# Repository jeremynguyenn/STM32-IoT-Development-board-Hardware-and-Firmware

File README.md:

Relate to this firmware git: https://github.com/jeremynguyenn/My-driver-Embedded-IoT-Frimware.git

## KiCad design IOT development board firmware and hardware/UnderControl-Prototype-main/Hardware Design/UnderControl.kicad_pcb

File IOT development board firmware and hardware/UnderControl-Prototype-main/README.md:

# STM32-GPS-GSM-IoT-Board-UnderControl-
IoT board to control smart home and car systems via Bluetooth, wifi, and GSM with embedded CAN transceiver for OBD.
Note: For Sch, Gerber and assembly files or any info you can contact me.

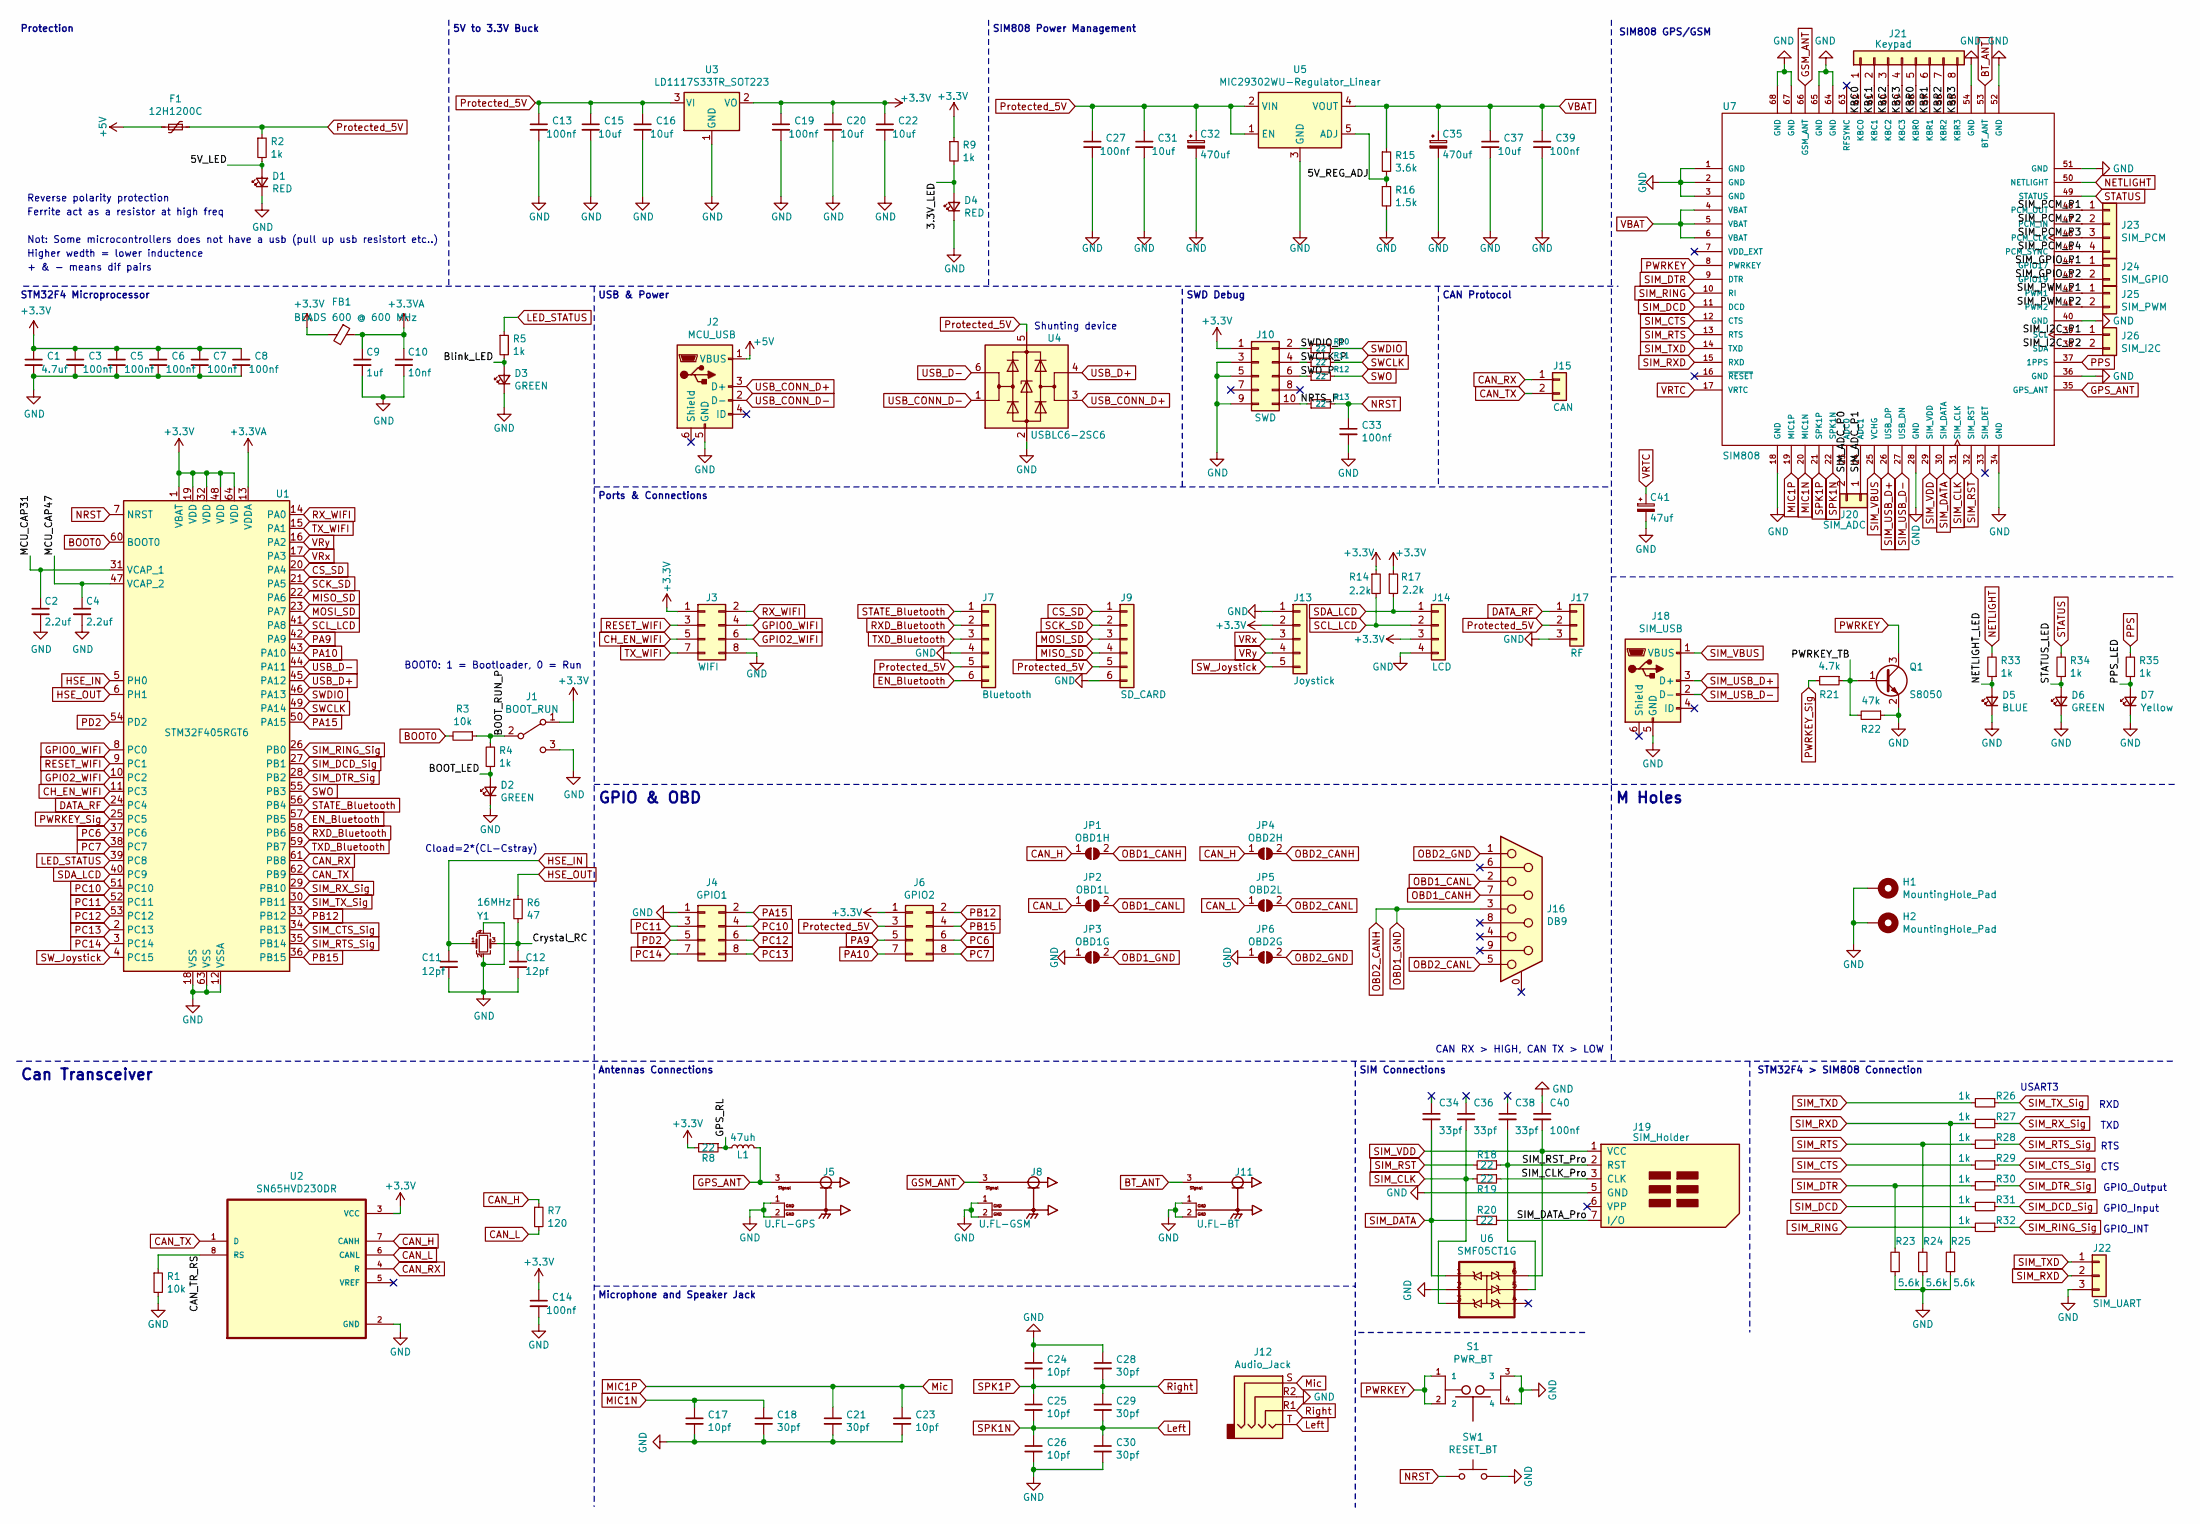
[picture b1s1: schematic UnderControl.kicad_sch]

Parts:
C1: 4.7uf; C_0603_1608Metric; LCSC Part # C19666
C2, C4: 2.2uf; C_0603_1608Metric; LCSC Part # C23630
C3, C5, C6, C7, C8, C13, C14, C19, C27, C33, C39, C40: 100nf; C_0402_1005Metric; LCSC Part # C1525
C9: 1uf; C_0402_1005Metric; LCSC Part # C52923
C10: 10nf; C_0402_1005Metric; LCSC Part # C15195
C11, C12: 12pf; C_0402_1005Metric; LCSC Part # C1547
C15, C16, C20, C22, C31: 10uf; C_0603_1608Metric; LCSC Part # C19702
C17, C23, C24, C25, C26: 10pf; C_0402_1005Metric; LCSC Part # C32949
C18, C21, C28, C29, C30: 30pf; C_0402_1005Metric; LCSC Part # C1570
C32, C35: 470uf; CP_Elec_8x10; LCSC Part # C176671
C34, C36, C38: 33pf; C_0402_1005Metric; LCSC Part # C1562
C37: 10uf; CP_EIA-3216-18_Kemet-A; LCSC Part # C7171
C41: 47uf; C_1206_3216Metric; LCSC Part # C96123
D1, D4: RED; D_0603_1608Metric; LCSC Part # C2286
D2, D6: GREEN; LED_0603_1608Metric; LCSC Part # C72043
D3: GREEN; D_0603_1608Metric; LCSC Part # C72043
D5: BLUE; LED_0603_1608Metric; LCSC Part # C72041
D7: Yellow; LED_0603_1608Metric; LCSC Part # C72038
F1: 12H1200C; Fuse_1206_3216Metric; LCSC Part # C182310
FB1: BEADS 600 @ 600 MHz; L_0805_2012Metric; LCSC Part # C1017
H1, H2: MountingHole_Pad; MountingHole_3.2mm_M3_Pad_Via
J1: BOOT_RUN; PinHeader_1x03_P2.54mm_Vertical
J2: MCU_USB; USB_Micro_JLCPCB; LCSC Part # C404969
J3: WIFI; PinSocket_2x04_P2.54mm_Vertical
J4: GPIO1; PinHeader_2x04_P2.54mm_Vertical
J5: U.FL-GPS; HRS_U.FL-R-SMT(01); LCSC Part # C88374
J6: GPIO2; PinHeader_2x04_P2.54mm_Vertical
J7: Bluetooth; PinSocket_1x06_P2.54mm_Vertical
J8: U.FL-GSM; HRS_U.FL-R-SMT(01); LCSC Part # C88374
J9: SD_CARD; PinSocket_1x06_P2.54mm_Vertical
J10: SWD; PinSocket_2x05_P2.54mm_Vertical
J11: U.FL-BT; HRS_U.FL-R-SMT(01); LCSC Part # C88374
J12: Audio_Jack; Jack_3.5mm_PJ320D_Horizontal
J13: Joystick; PinSocket_1x05_P2.54mm_Vertical
J14: LCD; PinSocket_1x04_P2.54mm_Vertical
J15: CAN; PinSocket_1x02_P2.54mm_Vertical
J16: DB9; DSUB-9_Female_Horizontal_P2.77x2.84mm_EdgePinOffset4.94mm_H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
J17: RF; PinHeader_1x03_P2.54mm_Vertical
J18: SIM_USB; USB_Micro_JLCPCB; LCSC Part # C404969
J19: SIM_Holder; FCI_7111S2015X02LF
J20: SIM_ADC; PinHeader_1x02_P2.54mm_Vertical
J21: Keypad; PinSocket_1x08_P2.54mm_Vertical
J22: SIM_UART; PinHeader_1x03_P2.54mm_Vertical
J23: SIM_PCM; PinHeader_1x04_P2.54mm_Vertical
J24: SIM_GPIO; PinHeader_1x02_P2.54mm_Vertical
J25: SIM_PWM; PinHeader_1x02_P2.54mm_Vertical
J26: SIM_I2C; PinHeader_1x02_P2.54mm_Vertical
JP1: OBD1H; PinHeader_1x02_P2.54mm_Vertical
JP2: OBD1L; PinHeader_1x02_P2.54mm_Vertical
JP3: OBD1G; PinHeader_1x02_P2.54mm_Vertical
JP4: OBD2H; PinHeader_1x02_P2.54mm_Vertical
JP5: OBD2L; PinHeader_1x02_P2.54mm_Vertical
JP6: OBD2G; PinHeader_1x02_P2.54mm_Vertical
L1: 47uh; L_0805_2012Metric; LCSC Part # C14304
Q1: S8050; SOT-23; LCSC Part # C2146
R1, R3: 10k; R_0603_1608Metric; LCSC Part # C25804
R2, R4, R5, R9, R26, R27, R28, R29, R30, R31, R32, R33, R34, R35: 1k; R_0603_1608Metric; LCSC Part # C21190
R6: 47; R_0402_1005Metric; LCSC Part # C25118
R7: 120; R_0603_1608Metric; LCSC Part # C22787
R8, R10, R11, R12, R13, R18, R19, R20: 22; R_0402_1005Metric; LCSC Part # C25092
R14, R17: 2.2k; R_0603_1608Metric; LCSC Part # C4190
R15: 3.6k; R_0603_1608Metric; LCSC Part # C22980
R16: 1.5k; R_0603_1608Metric; LCSC Part # C22843
R21: 4.7k; R_0603_1608Metric; LCSC Part # C23162
R22: 47k; R_0603_1608Metric; LCSC Part # C25819
R23, R24, R25: 5.6k; R_0603_1608Metric; LCSC Part # C23189
S1: PWR_BT; SW_TL3342F160QG
SW1: RESET_BT; SW_1437566-4
U1: STM32F405RGT6; LQFP-64_10x10mm_P0.5mm; LCSC Part # C15742
U2: SN65HVD230DR; SOIC127P599X175-8N; LCSC Part C12084
U3: LD1117S33TR_SOT223; SOT-223-3_TabPin2; LCSC Part C86781
U4: USBLC6-2SC6; SOT-23-6; LCSC Part # C7519
U5: MIC29302WU-Regulator_Linear; TO-263-5_TabPin3; LCSC Part C11149
U6: SMF05CT1G; SOT65P210X110-6N; LCSC Part # C15879
U7: SIM808; XCVR_SIM808
Y1: 16MHz; Crystal_SMD_3225-4Pin_3.2x2.5mm; LCSC Part # C13738

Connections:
+3.3VA: C9.1, C10.1, FB1.1, U1.13 (VDDA)
+3V3: C1.1, C3.1, C5.1, C6.1, C7.1, C8.1, C14.1, C19.1, C20.1, C22.1, FB1.2, J1.1 (A), J3.1, J6.1, J10.1, J13.2, J14.3, R8.2, R9.1, R14.1, R17.1, U1.1 (VBAT), U1.19 (VDD), U1.32 (VDD), U1.48 (VDD), U1.64 (VDD), U2.3 (VCC), U3.2 (VO)
+5V: F1.2, J2.1 (VBUS)
/3.3V_LED: D4.2 (A), R9.2
/5V_LED: D1.2 (A), R2.2
/5V_REG_ADJ: R15.2, R16.1, U5.5 (ADJ)
/BOOT_LED: D2.2 (A), R4.1
/BOOT_RUN_P: J1.2 (B), R3.1, R4.2
/Blink_LED: D3.2 (A), R5.2
/CAN_TR_RS: R1.1, U2.8 (RS)
/Crystal_RC: C12.1, R6.2, Y1.3
/GPS_RL: L1.1, R8.1
/KBC0: J21.1, U7.62 (KBC0)
/KBC1: J21.2, U7.61 (KBC1)
/KBC2: J21.3, U7.60 (KBC2)
/KBC3: J21.4, U7.59 (KBC3)
/KBR0: J21.5, U7.58 (KBR0)
/KBR1: J21.6, U7.57 (KBR1)
/KBR2: J21.7, U7.56 (KBR2)
/KBR3: J21.8, U7.55 (KBR3)
/MCU_CAP31: C2.1, U1.31 (VCAP_1)
/MCU_CAP47: C4.1, U1.47 (VCAP_2)
/NETLIGHT_LED: D5.2 (A), R33.1
/NRTS_P: J10.10, R13.1
/PPS_LED: D7.2 (A), R35.1
/PWRKEY_TB: Q1.1 (B), R21.1, R22.2
/SIM_ADC_P0: J20.2, U7.23 (ADC0)
/SIM_ADC_P1: J20.1, U7.24 (ADC1)
/SIM_CLK_Pro: J19.3 (CLK), R19.1
/SIM_DATA_Pro: J19.7 (I/O), R20.1
/SIM_GPIO_P1: J24.1, U7.44 (GPIO17)
/SIM_GPIO_P2: J24.2, U7.43 (GPIO19)
/SIM_I2C_P1: J26.1, U7.39 (SCL)
/SIM_I2C_P2: J26.2, U7.38 (SDA)
/SIM_PCM_P1: J23.1, U7.48 (PCM_OUT)
/SIM_PCM_P2: J23.2, U7.47 (PCM_IN)
/SIM_PCM_P3: J23.3, U7.46 (PCM_CLK)
/SIM_PCM_P4: J23.4, U7.45 (PCM_SYNC)
/SIM_PWM_P1: J25.1, U7.42 (PWM1)
/SIM_PWM_P2: J25.2, U7.41 (PWM2)
/SIM_RST_Pro: C38.2, J19.2 (RST), R18.1, U6.5
/STATUS_LED: D6.2 (A), R34.1
/SWCLK_P: J10.4, R11.1
/SWDIO_P: J10.2, R10.1
/SWO_P: J10.6, R12.1
BOOT0: R3.2, U1.60 (BOOT0)
BT_ANT: J11.3, U7.53 (BT_ANT)
CAN_H: JP1.1 (A), JP4.1 (A), R7.1, U2.7 (CANH)
CAN_L: JP2.1 (A), JP5.1 (A), R7.2, U2.6 (CANL)
CAN_RX: J15.1, U1.61 (PB8), U2.4 (R)
CAN_TX: J15.2, U1.62 (PB9), U2.1 (D)
CH_EN_WIFI: J3.5, U1.11 (PC3)
CS_SD: J9.1, U1.20 (PA4)
DATA_RF: J17.1, U1.24 (PC4)
EN_Bluetooth: J7.6, U1.57 (PB5)
GND: C1.2, C2.2, C3.2, C4.2, C5.2, C6.2, C7.2, C8.2, C9.2, C10.2, C11.2, C12.2, C13.2, C14.2, C15.2, C16.2, C17.2, C18.2, C19.2, C20.2, C21.2, C22.2, C23.2, C24.1, C26.2, C27.2, C28.1, C30.2, C31.2, C32.2, C33.2, C35.2, C37.2, C39.2, C40.1, C41.2, D1.1 (K), D2.1 (K), D3.1 (K), D4.1 (K), D5.1 (K), D6.1 (K), D7.1 (K), H1.1, H2.1, J1.3 (C), J2.5 (GND), J3.8, J4.1, J5.1, J5.2, J7.4, J8.1, J8.2, J9.6, J10.3, J10.5, J10.9, J11.1, J11.2, J12.R2, J13.1, J14.4, J17.3, J18.5 (GND), J19.5 (GND), J22.3, JP3.1 (A), JP6.1 (A), Q1.2 (E), R1.2, R16.2, R22.1, R23.1, R24.1, R25.1, S1.3, S1.4, SW1.2, U1.12 (VSSA), U1.18 (VSS), U1.63 (VSS), U2.2 (GND), U3.1 (GND), U4.2 (GND), U5.3 (GND), U6.2, U7.1 (GND), U7.2 (GND), U7.3 (GND), U7.18 (GND), U7.28 (GND), U7.34 (GND), U7.36 (GND), U7.40 (GND), U7.51 (GND), U7.52 (GND), U7.54 (GND), U7.64 (GND), U7.65 (GND), U7.67 (GND), U7.68 (GND), Y1.2, Y1.4
GPIO0_WIFI: J3.4, U1.8 (PC0)
GPIO2_WIFI: J3.6, U1.10 (PC2)
GPS_ANT: J5.3, L1.2, U7.35 (GPS_ANT)
GSM_ANT: J8.3, U7.66 (GSM_ANT)
HSE_IN: C11.1, U1.5 (PH0), Y1.1
HSE_OUT: R6.1, U1.6 (PH1)
LED_STATUS: R5.1, U1.39 (PC8)
Left: C25.2, C26.1, C29.2, C30.1, J12.T, U7.22 (SPK1N)
MIC1N: C17.1, C18.1, U7.20 (MIC1N)
MIC1P: C21.1, C23.1, J12.S, U7.19 (MIC1P)
MISO_SD: J9.4, U1.22 (PA6)
MOSI_SD: J9.3, U1.23 (PA7)
NETLIGHT: R33.2, U7.50 (NETLIGHT)
NRST: C33.1, R13.2, SW1.1, U1.7 (NRST)
OBD1_CANH: J16.7, JP1.2 (B)
OBD1_CANL: J16.2, JP2.2 (B)
OBD1_GND: J16.3, JP3.2 (B), JP4.2 (B)
OBD2_CANL: J16.5, JP5.2 (B)
OBD2_GND: J16.1, JP6.2 (B)
PA9: J6.5, U1.42 (PA9)
PA10: J6.7, U1.43 (PA10)
PA15: J4.2, U1.50 (PA15)
PB12: J6.2, U1.33 (PB12)
PB15: J6.4, U1.36 (PB15)
PC6: J6.6, U1.37 (PC6)
PC7: J6.8, U1.38 (PC7)
PC10: J4.4, U1.51 (PC10)
PC11: J4.3, U1.52 (PC11)
PC12: J4.6, U1.53 (PC12)
PC13: J4.8, U1.2 (PC13)
PC14: J4.7, U1.3 (PC14)
PD2: J4.5, U1.54 (PD2)
PPS: R35.2, U7.37 (1PPS)
PWRKEY: Q1.3 (C), S1.1, S1.2, U7.8 (PWRKEY)
PWRKEY_Sig: R21.2, U1.25 (PC5)
Protected_5V: C13.1, C15.1, C16.1, C27.1, C31.1, C32.1, F1.1, J6.3, J7.5, J9.5, J17.2, R2.1, U3.3 (VI), U4.5 (VBUS), U5.1 (EN), U5.2 (VIN)
RESET_WIFI: J3.3, U1.9 (PC1)
RXD_Bluetooth: J7.2, U1.58 (PB6)
RX_WIFI: J3.2, U1.14 (PA0)
Right: C24.2, C25.1, C28.2, C29.1, J12.R1, U7.21 (SPK1P)
SCK_SD: J9.2, U1.21 (PA5)
SCL_LCD: J14.2, R14.2, U1.41 (PA8)
SDA_LCD: J14.1, R17.2, U1.40 (PC9)
SIM_CLK: C36.2, R19.2, U6.3, U7.31 (SIM_CLK)
SIM_CTS: R29.2, U7.12 (CTS)
SIM_CTS_Sig: R29.1, U1.34 (PB13)
SIM_DATA: C34.2, R20.2, U6.1, U7.30 (SIM_DATA)
SIM_DCD: R31.2, U7.11 (DCD)
SIM_DCD_Sig: R31.1, U1.27 (PB1)
SIM_DTR: R23.2, R30.2, U7.9 (DTR)
SIM_DTR_Sig: R30.1, U1.28 (PB2)
SIM_RING: R32.2, U7.10 (RI)
SIM_RING_Sig: R32.1, U1.26 (PB0)
SIM_RST: R18.2, U7.32 (SIM_RST)
SIM_RTS: R24.2, R28.2, U7.13 (RTS)
SIM_RTS_Sig: R28.1, U1.35 (PB14)
SIM_RXD: J22.2, R25.2, R27.2, U7.15 (RXD)
SIM_RX_Sig: R27.1, U1.29 (PB10)
SIM_TXD: J22.1, R26.2, U7.14 (TXD)
SIM_TX_Sig: R26.1, U1.30 (PB11)
SIM_USB_D+: J18.3 (D+), U7.26 (USB_DP)
SIM_USB_D-: J18.2 (D-), U7.27 (USB_DN)
SIM_VBUS: J18.1 (VBUS), U7.25 (VCHG)
SIM_VDD: C40.2, J19.1 (VCC), U6.6, U7.29 (SIM_VDD)
STATE_Bluetooth: J7.1, U1.56 (PB4)
STATUS: R34.2, U7.49 (STATUS)
SWCLK: R11.2, U1.49 (PA14)
SWDIO: R10.2, U1.46 (PA13)
SWO: R12.2, U1.55 (PB3)
SW_Joystick: J13.5, U1.4 (PC15)
TXD_Bluetooth: J7.3, U1.59 (PB7)
TX_WIFI: J3.7, U1.15 (PA1)
USB_CONN_D+: J2.3 (D+), U4.3 (I/O2)
USB_CONN_D-: J2.2 (D-), U4.1 (I/O1)
USB_D+: U1.45 (PA12), U4.4 (I/O2)
USB_D-: U1.44 (PA11), U4.6 (I/O1)
VBAT: C35.1, C37.1, C39.1, R15.1, U5.4 (VOUT), U7.4 (VBAT), U7.5 (VBAT), U7.6 (VBAT)
VRTC: C41.1, U7.17 (VRTC)
VRx: J13.3, U1.17 (PA3)
VRy: J13.4, U1.16 (PA2)

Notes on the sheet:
Protection
STM32F4 Microprocessor
Can Transceiver
Reverse polarity protection
Ferrite act as a resistor at high freq
Not: Some microcontrollers does not have a usb (pull up usb resistort etc..)
Higher wedth = lower inductence
+ & - means dif pairs
BOOT0: 1 = Bootloader, 0 = Run
Cload=2*(CL-Cstray)
5V to 3.3V Buck
USB & Power
Ports & Connections
GPIO & OBD
Antennas Connections
Microphone and Speaker Jack
SIM808 Power Management
Shunting device
SWD Debug
SIM Connections
CAN RX > HIGH, CAN TX > LOW
CAN Protocol
M Holes
SIM808 GPS/GSM
STM32F4 > SIM808 Connection
USART3
GPIO_Output
GPIO_Input
GPIO_INT
RXD
TXD
RTS
CTS

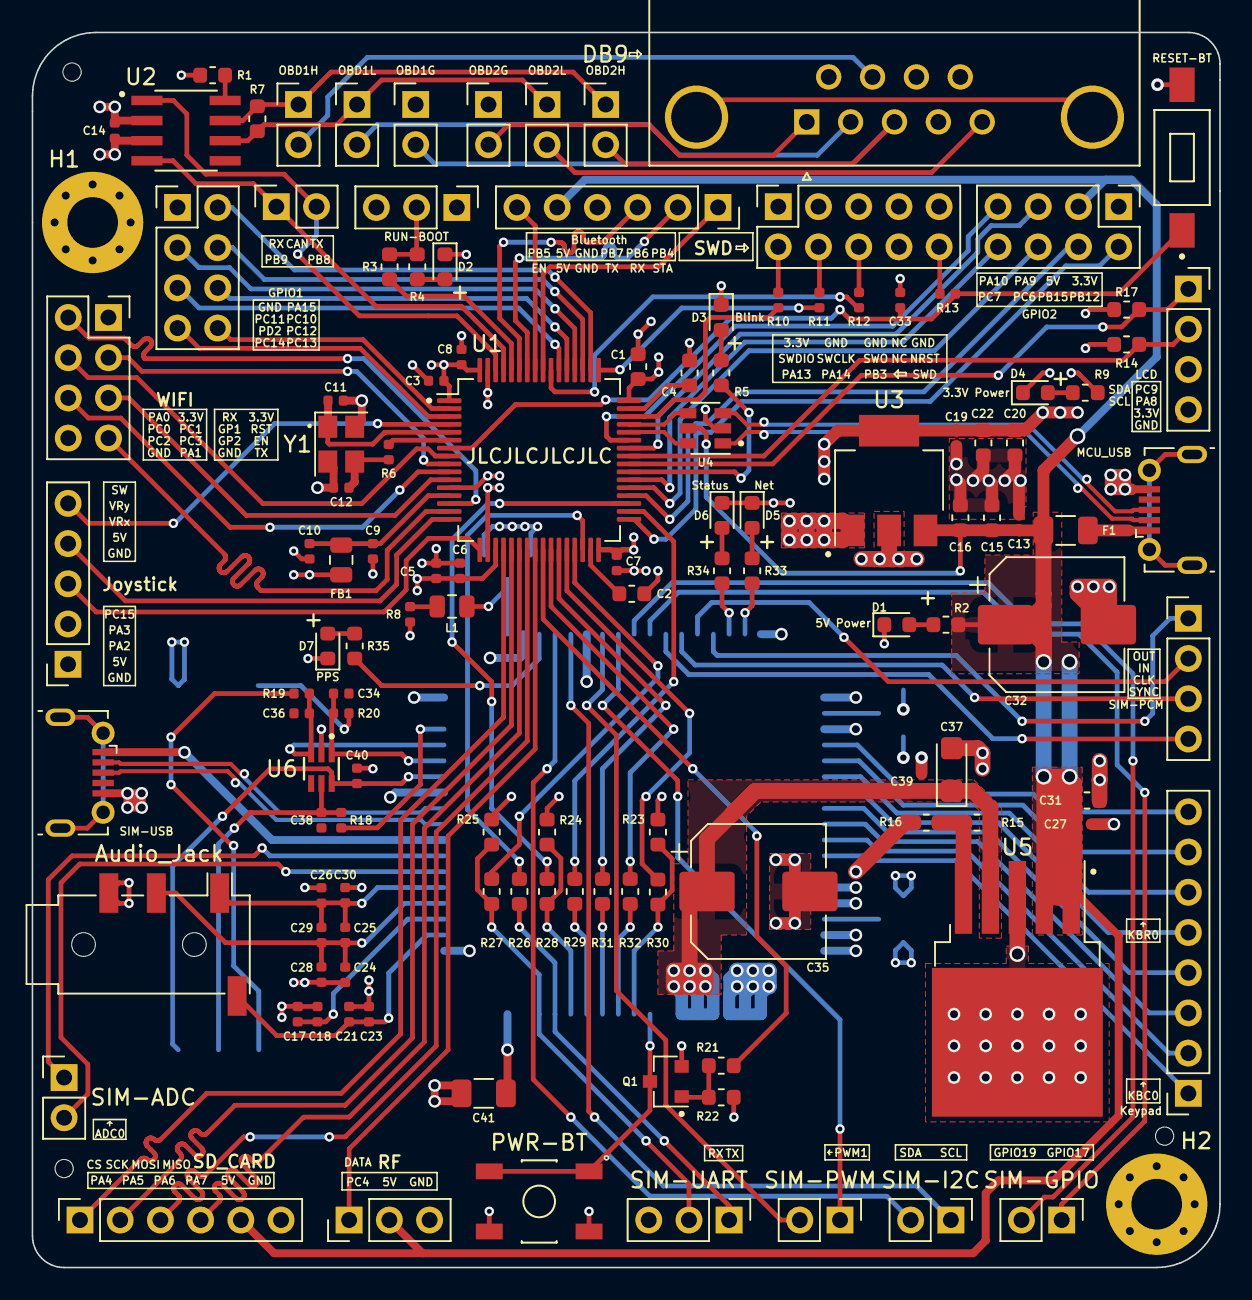
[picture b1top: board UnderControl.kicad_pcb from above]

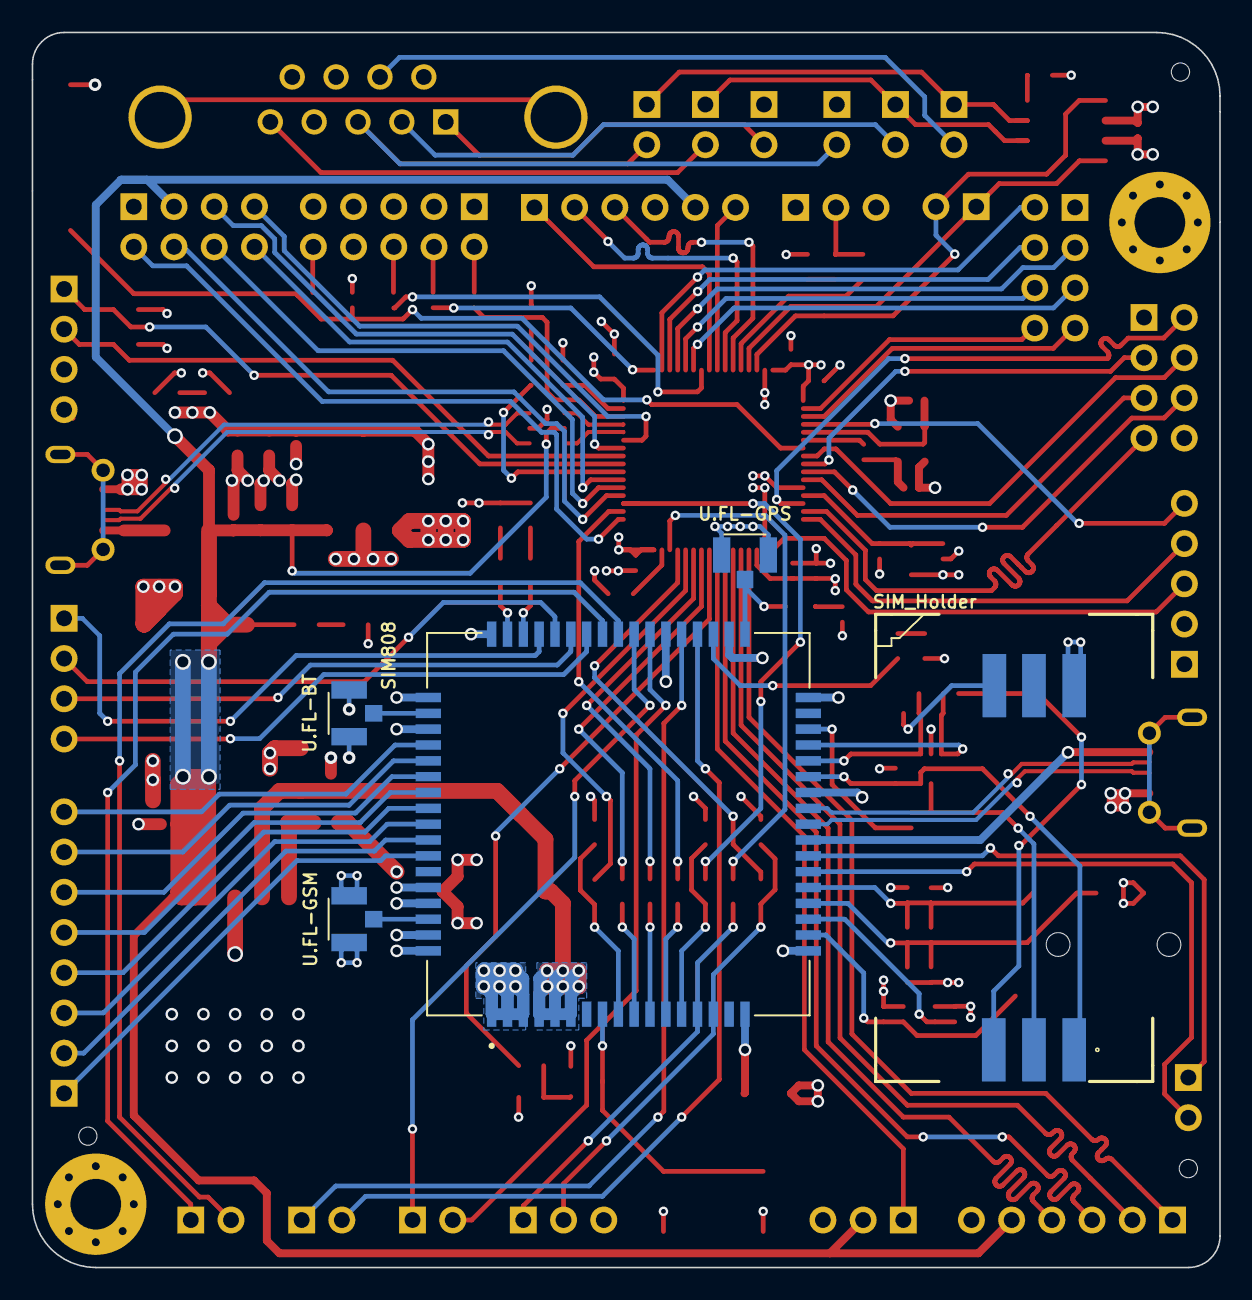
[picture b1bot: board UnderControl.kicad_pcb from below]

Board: 4 copper layers, 75.0 x 78.0 mm, 131 parts (5 on the bottom side), 136 nets.

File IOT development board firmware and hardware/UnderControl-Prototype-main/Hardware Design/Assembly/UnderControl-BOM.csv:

Comment,Designator,Footprint,LCSC Part #
4.7uf ,C1,C_0603_1608Metric,C19666
2.2uf ,"C2,C4",C_0603_1608Metric,C23630
100nf ,"C3,C5,C6,C7,C8,C13,C14,C19,C27,C33,C39,C40",C_0402_1005Metric,C1525
1uf ,C9,C_0402_1005Metric,C52923
10nf ,C10,C_0402_1005Metric,C15195
12pf ,"C11,C12",C_0402_1005Metric,C1547
10uf ,"C15,C16,C20,C22,C31",C_0603_1608Metric,C19702
10pf ,"C17,C23,C24,C25,C26",C_0402_1005Metric,C32949
30pf ,"C18,C21,C28,C29,C30",C_0402_1005Metric,C1570
470uf ,"C32,C35",CP_Elec_8x10,C176671
33pf ,"C34,C36,C38",C_0402_1005Metric,C1562
10uf ,C37,CP_EIA-3216-18_Kemet-A,C7171
47uf ,C41,C_1206_3216Metric,C96123
RED ,"D1,D4",D_0603_1608Metric,C2286
GREEN ,"D2,D6",LED_0603_1608Metric,C72043
GREEN ,D3,D_0603_1608Metric,C72043
BLUE ,D5,LED_0603_1608Metric,C72041
Yellow ,D7,LED_0603_1608Metric,C72038
12H1200C ,F1,Fuse_1206_3216Metric,C182310
BEADS 600 @ 600 MHz ,FB1,L_0805_2012Metric,C1017
MountingHole_Pad Mounting Hole with connection,"H1,H2",MountingHole_3.2mm_M3_Pad_Via,
BOOT_RUN ,J1,PinHeader_1x03_P2.54mm_Vertical,
MCU_USB USB Micro Type B connector,J2,USB_Micro_JLCPCB,C404969
WIFI ,J3,PinSocket_2x04_P2.54mm_Vertical,
"GPIO1 Generic connector, double row, 02x04, odd/even pin numbering scheme (row 1 odd numbers, row 2 even numbers), script generated (kicad-library-utils/schlib/autogen/connector/)",J4,PinHeader_2x04_P2.54mm_Vertical,
U.FL-GPS ,J5,HRS_U.FL-R-SMT(01),C88374
"GPIO2 Generic connector, double row, 02x04, odd/even pin numbering scheme (row 1 odd numbers, row 2 even numbers), script generated (kicad-library-utils/schlib/autogen/connector/)",J6,PinHeader_2x04_P2.54mm_Vertical,
Bluetooth ,J7,PinSocket_1x06_P2.54mm_Vertical,
U.FL-GSM ,J8,HRS_U.FL-R-SMT(01),C88374
SD_CARD ,J9,PinSocket_1x06_P2.54mm_Vertical,
SWD ,J10,PinSocket_2x05_P2.54mm_Vertical,
U.FL-BT ,J11,HRS_U.FL-R-SMT(01),C88374
"Audio_Jack Audio Jack, 4 Poles (TRRS)",J12,Jack_3.5mm_PJ320D_Horizontal,
Joystick ,J13,PinSocket_1x05_P2.54mm_Vertical,
LCD ,J14,PinSocket_1x04_P2.54mm_Vertical,
CAN ,J15,PinSocket_1x02_P2.54mm_Vertical,
"DB9 9-pin female D-SUB connector, Mounting Hole",J16,DSUB-9_Female_Horizontal_P2.77x2.84mm_EdgePinOffset4.94mm_Housed_MountingHolesOffset7.48mm,
RF ,J17,PinHeader_1x03_P2.54mm_Vertical,
SIM_USB USB Micro Type B connector,J18,USB_Micro_JLCPCB,C404969
SIM_Holder SIM Card,J19,FCI_7111S2015X02LF,
SIM_ADC ,J20,PinHeader_1x02_P2.54mm_Vertical,
Keypad ,J21,PinSocket_1x08_P2.54mm_Vertical,
SIM_UART ,J22,PinHeader_1x03_P2.54mm_Vertical,
SIM_PCM ,J23,PinHeader_1x04_P2.54mm_Vertical,
SIM_GPIO ,J24,PinHeader_1x02_P2.54mm_Vertical,
SIM_PWM ,J25,PinHeader_1x02_P2.54mm_Vertical,
SIM_I2C ,J26,PinHeader_1x02_P2.54mm_Vertical,
"OBD1H Solder Jumper, 2-pole, open",JP1,PinHeader_1x02_P2.54mm_Vertical,
"OBD1L Solder Jumper, 2-pole, open",JP2,PinHeader_1x02_P2.54mm_Vertical,
"OBD1G Solder Jumper, 2-pole, open",JP3,PinHeader_1x02_P2.54mm_Vertical,
"OBD2H Solder Jumper, 2-pole, open",JP4,PinHeader_1x02_P2.54mm_Vertical,
"OBD2L Solder Jumper, 2-pole, open",JP5,PinHeader_1x02_P2.54mm_Vertical,
"OBD2G Solder Jumper, 2-pole, open",JP6,PinHeader_1x02_P2.54mm_Vertical,
47uh ,L1,L_0805_2012Metric,C14304
S8050 ,Q1,SOT-23,C2146
10k ,"R1,R3",R_0603_1608Metric,C25804
1k ,"R2,R4,R5,R9,R26,R27,R28,R29,R30,R31,R32,R33,R34,R35",R_0603_1608Metric,C21190
47 ,R6,R_0402_1005Metric,C25118
120 ,R7,R_0603_1608Metric,C22787
22 ,"R8,R10,R11,R12,R13,R18,R19,R20",R_0402_1005Metric,C25092
2.2k ,"R14,R17",R_0603_1608Metric,C4190
3.6k ,R15,R_0603_1608Metric,C22980
1.5k ,R16,R_0603_1608Metric,C22843
4.7k ,R21,R_0603_1608Metric,C23162
47k ,R22,R_0603_1608Metric,C25819
5.6k ,"R23,R24,R25",R_0603_1608Metric,C23189
PWR_BT ,S1,SW_TL3342F160QG,
"RESET_BT Push button switch, generic, two pins",SW1,SW_1437566-4,
STM32F405RGT6 ,U1,LQFP-64_10x10mm_P0.5mm,C15742
SN65HVD230DR ,U2,SOIC127P599X175-8N,C12084
"LD1117S33TR_SOT223 800mA Fixed Low Drop Positive Voltage Regulator, Fixed Output 3.3V, SOT-223",U3,SOT-223-3_TabPin2,C86781
USBLC6-2SC6 ,U4,SOT-23-6,C7519
MIC29302WU-Regulator_Linear ,U5,TO-263-5_TabPin3,C11149
SMF05CT1G ,U6,SOT65P210X110-6N,C15879
SIM808 ,U7,XCVR_SIM808,
16MHz ,Y1,Crystal_SMD_3225-4Pin_3.2x2.5mm,C13738
